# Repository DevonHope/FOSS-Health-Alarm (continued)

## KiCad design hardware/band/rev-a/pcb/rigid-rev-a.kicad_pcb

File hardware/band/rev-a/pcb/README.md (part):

# WakeBand rigid rev A (KiCad project)

4-layer 0.8 mm rigid board that replaces the flex design (archived in
`../../archive/flex-rev-a`). Routed, DRC clean, fab package in `fab/`. Last edited with
KiCad 10.0.3 (earlier revisions used 10.0.5; the file format is the same).

> **Before ordering rev A** (review 2026-11-08, `../../../reviews/2026-11-08`): the four layout items the
> review found were **fixed on 2026-11-08** by `scripts/review_fixes_2026_11_08.py`, and `fab/` was re-plotted
> (`scripts/mkfab.py`):
> - C203 pad 2 (GND, 116.12, 111.22) had one thermal spoke into GND_L1 (KiCad 10 `starved_thermal`): the
>   pad is boxed in by the PMIC_INT track, the SWDIO and VDD_2V0 vias and C203 pad 1, so it now has a solid
>   zone connection. Like R202.2, C401.2, R605.2 and C403.2 (review A-L2), that is a small tombstoning risk.
> - U202 (KTD2026): exposed pad 1.45 x 0.8 -> 1.2 x 0.65 mm, footprint renamed
>   `Kinetic_UTDFN-8_1.5x1.5mm_P0.4mm_EP1.2x0.65mm`. KiCad's DFN-8 pad is 0.7 x 1.2; 0.65 across the pin rows
>   keeps 0.2 mm to these 0.45 mm pins (0.7 would leave 0.175). Paste on the EP is two 0.45 x 0.48 mm
>   windows, 55 %. The pins, their tracks and the EP's GND link are unchanged.
> - The reference text of C208, U202 and D702, which was plotted 110-230 mm off the board in the top
>   silkscreen, is now on F.Fab next to each part, like the other references. No Gerber has anything outside
>   the outline.
> - The SWDCLK dock pad's via moved from the pad centre, where the spring pin lands, to the pad's left edge
>   (130.65, 101.1), on its F.Cu track, like the VIN and GND pads' edge vias.

| Item | Value |
| --- | --- |
| Board | 33 x 15 mm, 1 mm corner radius, 0.8 mm FR4, ENIG |
| Pod | printed case rev A in `../case` (one M2 screw); see below for the height stack |
| DRC | 0 violations, 0 unconnected, schematic parity 0 (1 documented exclusion); off-centre via ends checked as errors |
| Traces | straight or 45-degree segments only, 45-degree bends, every end on its pad or via centre (audit 2026-11-06, below) |
| ERC | 0 errors, 0 warnings |
| Vias | 140: 129 x 0.45/0.3 mm, 11 x 0.3/0.2 mm |
| Files | `rigid-rev-a-layout.pdf` (layers), `rigid-rev-a.pdf` (schematic), `fab/` |

## Stackup

JLCPCB JLC04081H-7628, 0.8 mm (also in `fab/gerbers/rigid-rev-a-job.gbrjob`):

| Layer | Use |
| --- | --- |
| F.Cu (L1, 35 um) | all SMT parts, two UART bench pads (J601 5-6, top edge), signal fan-out, GND pour |
| prepreg 7628, 0.21 mm | |
| In1.Cu (L2, 15 um) | solid GND, no tracks; no copper in the antenna keep-out |
| core 0.26 mm | |
| In2.Cu (L3, 15 um) | power jumps (VSYS, VBAT, VIN, VDD_2V0, LRA_P, nRESET) and signal routing; GND fill in the spare area |
| prepreg 7628, 0.21 mm | |
| B.Cu (L4, 35 um) | faces the cell and LRA: the four dock landing pads (J601 1-4), hand-solder pads TP201/TP202/TP501/TP502, JP201, signal routing, GND pour; no parts |

Track length by layer: F.Cu 208 mm, In2.Cu 205 mm, B.Cu 147 mm, In1.Cu 0.

## Orientation, outline and pod height

The board mounts **parts-side out** (changed 2026-11-06): F.Cu, with every
part, faces the case top, the pod's outer face. B.Cu has no parts and faces
the cell and the LRA, which sit between the board and the wrist.

**Dock contacts (changed 2026-11-07): four landing pads on B.** J601 pads
1-4 are Ø1.6 mm ENIG pads on B.Cu in a column at x 131.5, beside the LRA:
SWDCLK (y 101.1), SWDIO (103.3), GND (111.7), VIN (113.9). Four Mill-Max
0906-2 spring pins on the contact carrier in the wrist cover press on them
(see `../case` and `../contact-carrier`); nothing is soldered to
them. J601 pads 5-6 (UART_RX x 123.75, UART_TX x 121.75, y 101.6) stay on F
as bench test pads; the dock no longer carries UART (it uses SWD + RTT).
Coordinates below are KiCad board coordinates, with the board from
(100, 100) to (133, 115). The strip along the top edge (x 119.8-133) has
no parts, so the case top's land sits right on the board there and takes
the push of the top pair of spring pins.

Pod height, from the outer face (case rev A):

| Layer | mm |
| --- | --- |
| case top | 1.2 |
| tallest F part (L201, 0603 caps, SOD-123F) plus 0.2 mm | 1.3 |
| board | 0.8 |
| gap (B.Cu has no parts) | 0.2 |
| cell, up to | 5.0 |
| foam | 0.5 |
| wrist cover floor | 1.0 |
| **Total** | **about 10** (9 with a 4 mm cell) |

## Envelopes (Dwgs.User)

| Envelope | Where | Notes |
| --- | --- | --- |
| ISP2454 antenna keep-out | x 100-105, full height | rule area inside the U1 footprint: no tracks, vias or pours on any layer |
| 60 mAh cell, 17 x 13.5 mm | x 107-124, y 100.75-114.25 | under B; starts 2 mm past the keep-out; PCM and lead end at x = 124 |
| Ø8 LRA (Ø8.5 envelope) | centre (128.75, 107.5), x 124.5-133 | under B, far end of the board; circle top at y 103.25, bottom at 111.75 |

## 3D models

Every part on the board has a 3D model, except the test pads, the dock
pads, NT201 and JP201, which need none. KiCad 10 has no model for two
footprints, so `wakeband.3dshapes/` holds parametric ones (build123d; rebuild
with `pip install build123d`, then from this folder
`python wakeband.3dshapes/make_models.py wakeband.3dshapes`):

| Model | Used by | Size and source |
| --- | --- | --- |
| `InsightSiP_ISP2454_LGA-62_8x8mm.step` | U1 (also set in `wakeband.pretty`) | 8 x 8 x 1.0 mm, substrate plus overmould, pin-1 dot; size from the footprint |
| `Texas_DPY0002A_0.6x1mm_P0.65mm.step` | D602-D605 | 1.0 x 0.6 x 0.375 mm X1SON-2, bottom terminals, pin-1 band; TI MPSS034C |
| `LiPo_3.7V_60mAh_401215_PCM.step` | cell (off board) | 17 x 13 x 4.0 mm pouch with folded PCM at +X, lead stubs |
| `Vybronics_VG0832012_LRA_D8x3.25mm.step` | LRA (off board) | Ø8.0 x 3.25 mm can, lead tab at +X |
| `LED_TOGIALED_1615_RGB_CommonAnode.step` | D702 | 1.6 x 1.5 x 0.6 mm body and lens, pin-1 (anode) mark |
| `Kinetic_UTDFN-8_1.5x1.5mm_P0.4mm_EP1.45x0.8mm.step` | U202 (footprint now `..._EP1.2x0.65mm`; the package is the same) | 1.5 x 1.5 x 0.5 mm UTDFN-8, pin-1 dot, terminals |

The paths use `${KIPRJMOD}`. D602-D605 use the KiCad library footprint
`Package_SON:Texas_DPY0002A_0.6x1mm_P0.65mm`; "Update footprint from library"
puts back the library's model path, which has no file in KiCad 10.

`make_placed.py` places the cell and the LRA in the board's STEP frame,
under B.Cu with a 0.2 mm gap: the cell centred at (115.5, 107.5) with its
lead end at x = 124, and the LRA centred at (128.75, 107.5) with its lead tab
turned towards TP501. The leads run to TP201 (bottom right) and TP202 (top
right) and to TP501/TP502. A clash check against the board's STEP finds no
overlaps. The tallest F part is now 1.1 mm (SW201 was removed on
2026-11-07); the charge LED is 0.6 mm.

## Placement

- **U1 ISP2454** at the left end, antenna end in the keep-out strip.
- **U401 LIS2DW12** just right of the module's top corner. C401 and C402
  sit right of it, 1.0 mm of track from pins 9 and 10; their GND pads share
  one via, and U401's GND pads 5-8 share another.
- **U201 nPM1304** in the middle. The BUCK1 parts sit left of it (see
  "Buck loop" below).
- **Charger caps** stacked right of U201, each beside its pin: C206
  (VBUSOUT, pin 22), C201 (VIN, pin 21), C205 (VSYS, pin 20), C202 (VBAT,
  pin 19). Their GND pads are joined by an F.Cu spine with three vias to
  In1 between the pads. R202 (VSET1) and R201 (DNP) sit below the stack.
  C203 sits under PMIC pin 12, offset left so pins 13-15 can escape.
- **JP201** (I_BAT jumper) on B in the bottom-right corner, between the
  cell's lead end and TP201, outside the cell and LRA outlines, so it can
  be cut for current measurement with the cell fitted.
- **Dock landing pads** J601 on B at x 131.5 (see Orientation). Their
  protection parts stay along the bottom edge: R601-R604 and D602-D605 (TI
  DPY package) between the module and D601 (VIN TVS).
- **U501 DRV2605L** at the right end over the LRA envelope, with C501, C502.
- **Hand-solder pads** on B (the cell side), 0.5 mm to other copper and
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
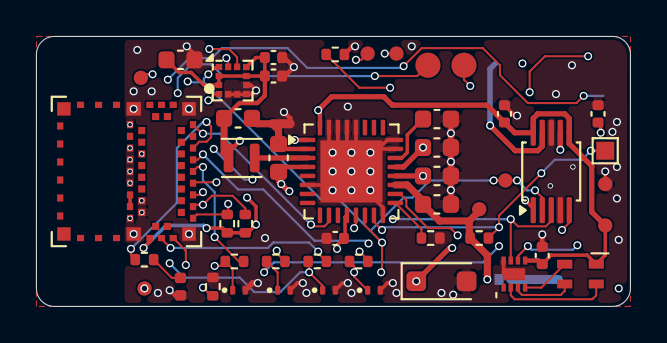
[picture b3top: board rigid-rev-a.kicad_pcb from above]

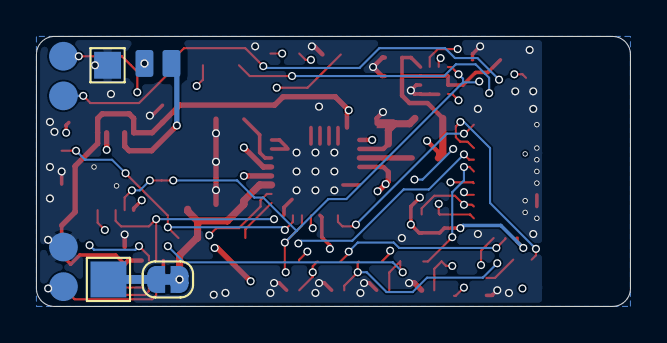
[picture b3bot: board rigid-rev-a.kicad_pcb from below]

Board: 4 copper layers, 33.0 x 15.0 mm, 53 parts (5 on the bottom side), 36 nets.

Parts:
C201, C206: 1uF 50V X5R; C_0603_1608Metric
C202: 2.2uF 16V X5R; C_0603_1608Metric
C203, C401, C402: 100nF; C_0402_1005Metric
C204, C205, C207, C403: 10uF 25V X5R; C_0603_1608Metric
C208, C501, C502: 1uF 25V X5R; C_0402_1005Metric
D601: SMF12A (TVS); D_SOD-123F
D602, D603, D604, D605: TPD1E10B06; Texas_DPY0002A_0.6x1mm_P0.65mm
D701: red DNP; LED_0402_1005Metric
D702: TJ-S1615SW6TGLCCYRGB-A5; LED_TOGIALED_1615_RGB_CommonAnode
J601: Dock landing pads; DockLanding_4xB_D1.6mm_2xUART
JP201: I_BAT; SolderJumper-2_P1.3mm_Bridged_RoundedPad1.0x1.5mm
L201: 2.2uH; L_Murata_DFE201610P
NT201: NetTie; NetTie-2_SMD_Pad0.5mm
R201: 100k DNP; R_0402_1005Metric
R202: 68k 1%; R_0402_1005Metric
R203, R204: 4.7k; R_0402_1005Metric
R601, R602, R603, R604: 100; R_0402_1005Metric
R605: 100k; R_0402_1005Metric
R701: 1k DNP; R_0402_1005Metric
TH201: 10k B3380; R_0402_1005Metric
TP201: BAT+ pad; TestPoint_Pad_2.0x2.0mm
TP202: BAT- pad; TestPoint_Pad_1.5x1.5mm
TP203: SHPHLD; TestPoint_Pad_1.0x1.0mm
TP401: ACC_INT2; TestPoint_Pad_D0.8mm
TP501: LRA+; Pad_SMD_1.0x1.5mm
TP502: LRA-; Pad_SMD_1.0x1.5mm
TP701: nRESET; TestPoint_Pad_D0.8mm
TP702: I2C_SDA; TestPoint_Pad_D0.8mm
TP703: I2C_SCL; TestPoint_Pad_D0.8mm
TP704: VDD_2V0; TestPoint_Pad_D0.8mm
TP705: VSYS; TestPoint_Pad_D0.8mm
TP706: VBAT; TestPoint_Pad_D0.8mm
TP707: GND; TestPoint_Pad_D0.8mm
U1: ISP2454-LX; InsightSiP_ISP2454_LGA-62_8x8mm
U201: nPM1304-QEAA; QFN-32-1EP_5x5mm_P0.5mm_EP3.45x3.45mm
U202: KTD2026EWE-TR; Kinetic_UTDFN-8_1.5x1.5mm_P0.4mm_EP1.2x0.65mm
U401: LIS2DW12TR; LGA-12_2x2mm_P0.5mm
U501: DRV2605LDGSR; TSSOP-10_3x3mm_P0.5mm

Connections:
/debug/LED_A: D701.2, R701.2
/dock/PAD_RX: D604.1, J601.5, R603.1
/dock/PAD_SWDCLK: D602.1, J601.3, R601.1
/dock/PAD_SWDIO: D603.1, J601.4, R602.1
/dock/PAD_TX: D605.1, J601.6, R604.1
/haptics/LRA_N: TP502.1, U501.9
/haptics/LRA_P: TP501.1, U501.7
/haptics/REG: C502.1, U501.1
/power/BATT_P: JP201.1, TP201.1
/power/LED_B: D702.2, U202.4
/power/LED_G: D702.3, U202.3
/power/LED_R: D702.4, U202.2
/power/NTC: TH201.1, U201.18
/power/PVSS1: C204.2, C207.2, NT201.1, U201.2
/power/SHPHLD: R201.2, TP203.1, U201.15
/power/SW1: L201.1, U201.3
/power/VBUSOUT: C206.1, U201.22
/power/VSET1: R202.1, U201.17
ACC_INT1: U1.36, U401.12
ACC_INT2: TP401.1, U401.11
ANT_LINK: U1.20, U1.22
GND: C201.2, C202.2, C203.2, C205.2, C206.2, C208.2, C401.2, C402.2, C403.2, C501.2, C502.2, D601.2, D602.2, D603.2, D604.2, D605.2, D701.1, J601.2, NT201.2, R202.2, R605.2, TH201.2, TP202.1, TP707.1, U1.1, U1.7, U1.8, U1.12, U1.14, U1.16, U1.18, U1.21, U1.23, U1.24, U1.25, U1.31, U201.6, U201.16, U201.23, U201.24, U201.28, U201.29, U201.30, U201.31, U201.33, U202.8, U202.9, U401.5, U401.6, U401.7, U401.8, U501.4, U501.8
HAPT_EN: U1.42, U501.5
I2C_SCL: R204.2, TP703.1, U1.34, U201.14, U202.6, U401.1, U501.2
I2C_SDA: R203.2, TP702.1, U1.32, U201.13, U202.7, U401.4, U501.3
LED_DBG: R701.1, U1.44
PMIC_INT: U1.48, U201.10
SWDCLK: R601.2, U1.30
SWDIO: R602.2, U1.28
UART_RX: R603.2, R605.1, U1.38
UART_TX: R604.2, U1.40
VBAT: C202.1, JP201.2, R201.1, TP706.1, U201.19
VDD_2V0: C203.1, C207.1, C401.1, C402.1, C403.1, L201.2, R203.1, R204.1, TP704.1, U1.26, U201.1, U201.12, U401.2, U401.3, U401.9, U401.10
VIN: C201.1, D601.1, J601.1, U201.21
VSYS: C204.1, C205.1, C208.1, C501.1, D702.1, TP705.1, U201.4, U201.20, U201.32, U202.5, U501.6, U501.10
nRESET: TP701.1, U1.13

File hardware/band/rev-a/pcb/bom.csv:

"Comment","Designator","Footprint","LCSC","MPN","Qty","DNP"
"1uF 50V X5R","C201,C206","Capacitor_SMD:C_0603_1608Metric","C15849","","2",""
"2.2uF 16V X5R","C202","Capacitor_SMD:C_0603_1608Metric","C23630","","1",""
"100nF","C203,C401,C402","Capacitor_SMD:C_0402_1005Metric","C1525","","3",""
"10uF 25V X5R","C204,C205,C207,C403","Capacitor_SMD:C_0603_1608Metric","C96446","","4",""
"1uF 25V X5R","C208,C501,C502","Capacitor_SMD:C_0402_1005Metric","C52923","","3",""
"SMF12A (TVS)","D601","Diode_SMD:D_SOD-123F","C207255","Littelfuse SMF12A","1",""
"TPD1E10B06","D602,D603,D604,D605","Package_SON:Texas_DPY0002A_0.6x1mm_P0.65mm","C48260","TI TPD1E10B06DPYR","4",""
"TJ-S1615SW6TGLCCYRGB-A5 (RGB LED, common anode)","D702","wakeband:LED_TOGIALED_1615_RGB_CommonAnode","C273610","TOGIALED TJ-S1615SW6TGLCCYRGB-A5","1",""
"red DNP","D701","LED_SMD:LED_0402_1005Metric","C25503345","XINGLIGHT XL-1005SURC","1","DNP"
"2.2uH","L201","Inductor_SMD:L_Murata_DFE201610P","C337891","Murata DFE201610E-2R2M","1",""
"100k DNP","R201","Resistor_SMD:R_0402_1005Metric","C25741","","1","DNP"
"68k 1%","R202","Resistor_SMD:R_0402_1005Metric","C36871","","1",""
"4.7k","R203,R204","Resistor_SMD:R_0402_1005Metric","C25900","","2",""
"100","R601,R602,R603,R604","Resistor_SMD:R_0402_1005Metric","C25076","","4",""
"100k","R605","Resistor_SMD:R_0402_1005Metric","C25741","","1",""
"1k DNP","R701","Resistor_SMD:R_0402_1005Metric","C11702","","1","DNP"
"10k B3380","TH201","Resistor_SMD:R_0402_1005Metric","C77131","Murata NCP15XH103F03RC","1",""
"ISP2454-LX","U1","wakeband:InsightSiP_ISP2454_LGA-62_8x8mm","","","1",""
"nPM1304-QEAA","U201","Package_DFN_QFN:QFN-32-1EP_5x5mm_P0.5mm_EP3.45x3.45mm","","","1",""
"KTD2026EWE-TR (I2C RGB LED driver; Digi-Key, no LCSC listing)","U202","wakeband:Kinetic_UTDFN-8_1.5x1.5mm_P0.4mm_EP1.45x0.8mm","","Kinetic KTD2026EWE-TR","1",""
"LIS2DW12TR","U401","Package_LGA:LGA-12_2x2mm_P0.5mm","C189624","","1",""
"DRV2605LDGSR","U501","Package_SO:TSSOP-10_3x3mm_P0.5mm","C527464","","1",""
"60mAh 3.7V protected LiPo, ~16x13x4-5 mm, wire leads (hand-soldered to TP201/TP202, not assembled; alt. Ampul 401215)","BT1 (off-board)","","","X2 Robotics 3.7V 60mAh LiPo","1","not assembled"

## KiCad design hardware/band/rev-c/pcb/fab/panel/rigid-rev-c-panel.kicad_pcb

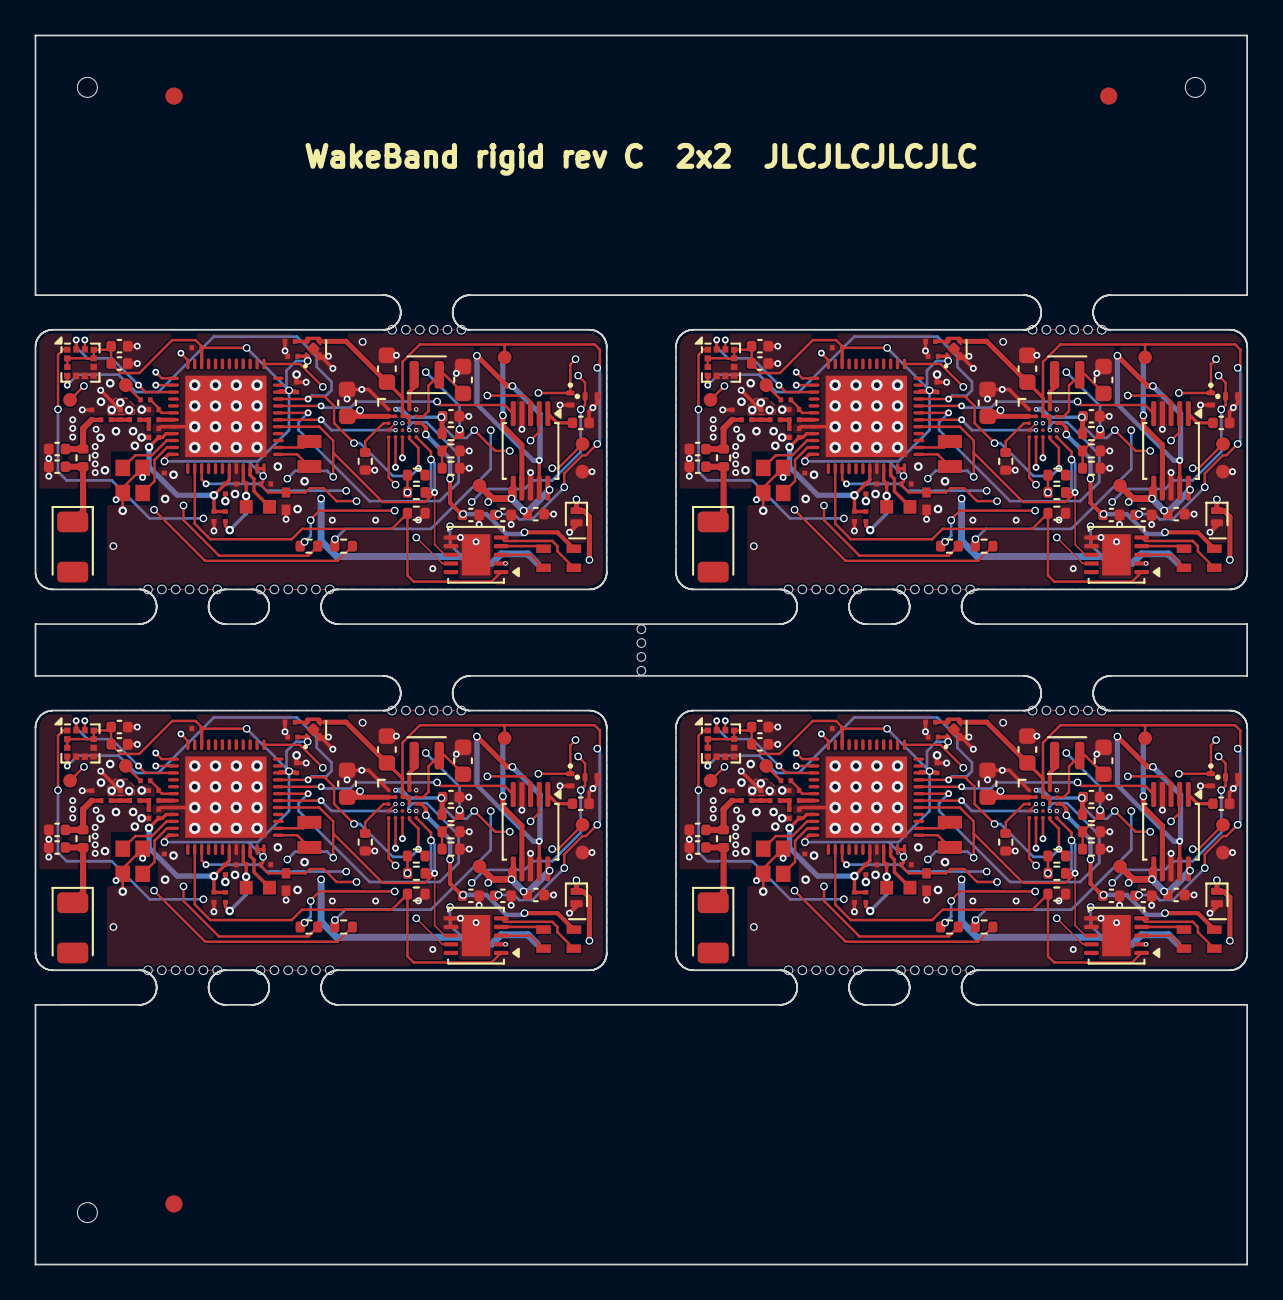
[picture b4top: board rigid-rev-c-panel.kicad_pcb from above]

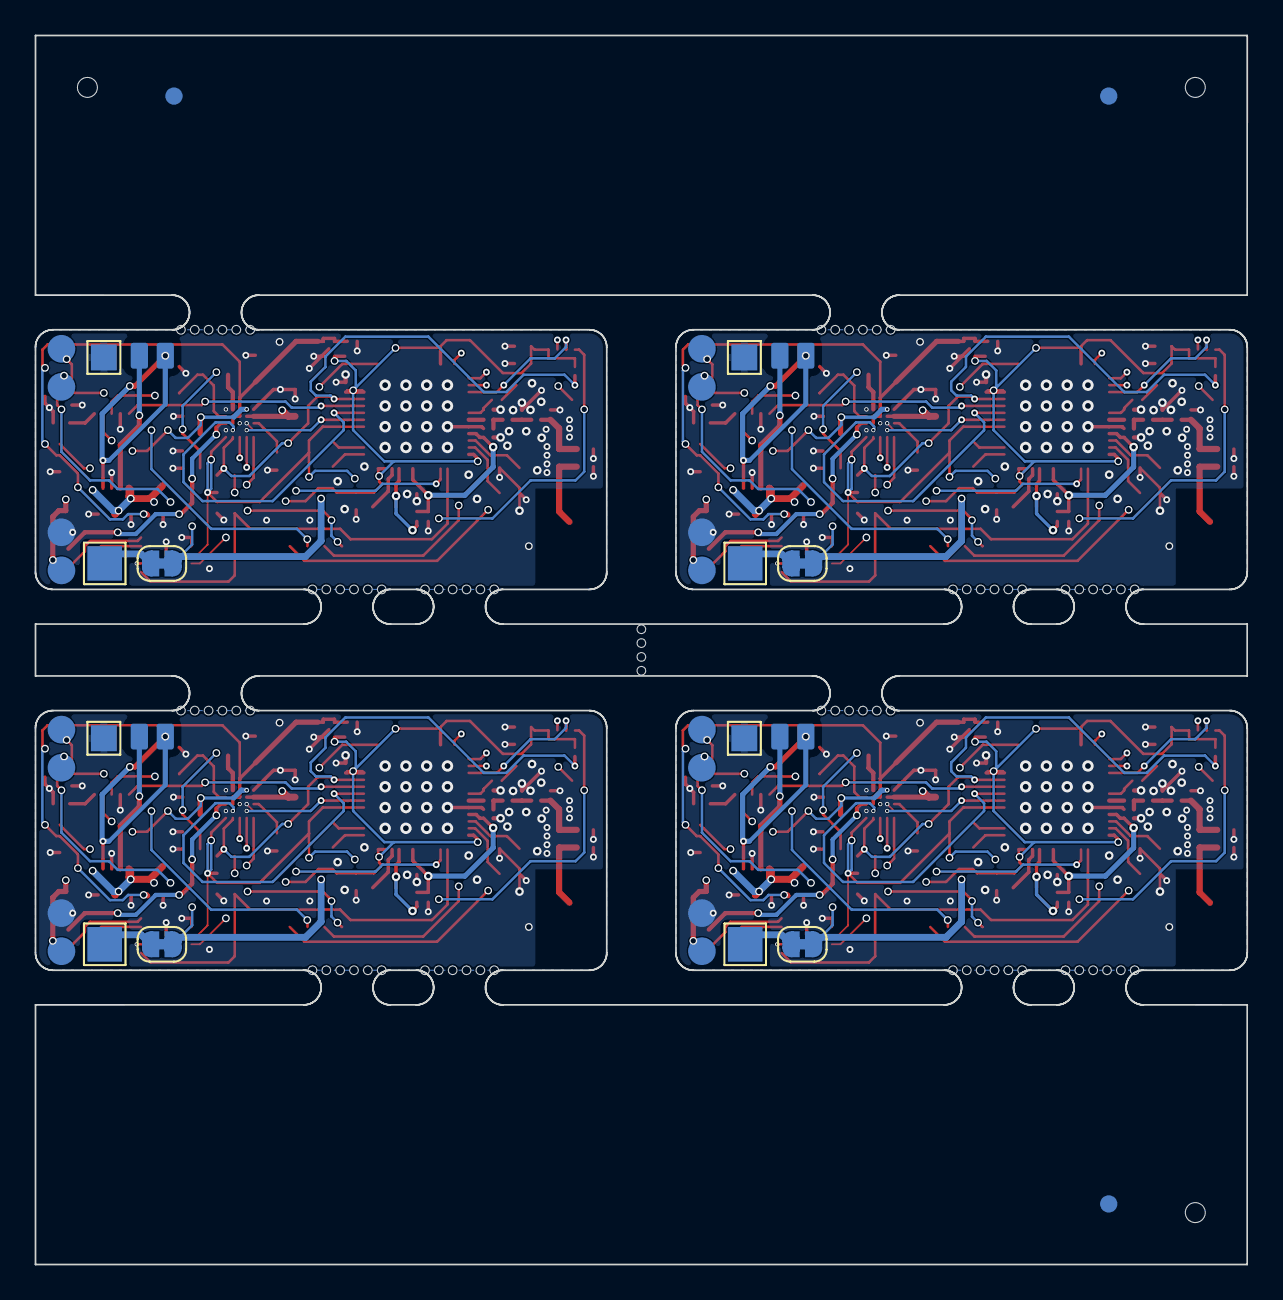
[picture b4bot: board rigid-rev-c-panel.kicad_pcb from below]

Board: 4 copper layers, 70.0 x 71.0 mm, 361 parts (23 on the bottom side), 184 nets.

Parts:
AE1_0, AE1_1, AE1_2, AE1_3: 2450AT18A0100001E; Johanson_2450AT18x100
C1_0, C1_1, C1_2, C1_3, C2_0, C2_1, C2_2, C2_3: 2.2uF; Nordic_CAPC0603X03L_C
C3_0, C3_1, C3_2, C3_3: 10uF; Nordic_CAPC1005X04L
C4_0, C4_1, C4_2, C4_3, C7_0, C7_1, C7_2, C7_3, C8_0, C8_1, C8_2, C8_3, C10_0, C10_1, C10_2, C10_3: 100nF; Nordic_CAPC0603X03L_C
C5_0, C5_1, C5_2, C5_3: 2.2nF; Nordic_CAPC0603X03L_C
C6_0, C6_1, C6_2, C6_3: 1.5pF; Nordic_CAPC0603X03L_C
C9_0, C9_1, C9_2, C9_3: 2.0pF; Nordic_CAPC0603X03L_C
C11_0, C11_1, C11_2, C11_3: 0.3pF; Nordic_CAPC0603X03L_C
C12_0, C12_1, C12_2, C12_3: 10nF; Nordic_CAPC0603X03L_C
C13_0, C13_1, C13_2, C13_3: 3.9pF; Nordic_CAPC0603X03L_C
C14_0, C14_1, C14_2, C14_3, C15_0, C15_1, C15_2, C15_3: DNP; C_0402_1005Metric
C201_0, C201_1, C201_2, C201_3, C208_0, C208_1, C208_2, C208_3, C501_0, C501_1, C501_2, C501_3, C502_0, C502_1, C502_2, C502_3: 1uF; C_0402_1005Metric
C202_0, C202_1, C202_2, C202_3: 2.2uF; C_0603_1608Metric
C205_0, C205_1, C205_2, C205_3, C206_0, C206_1, C206_2, C206_3: 10uF; C_0603_1608Metric
C209_0, C209_1, C209_2, C209_3, C401_0, C401_1, C401_2, C401_3, C402_0, C402_1, C402_2, C402_3: 100nF; C_0402_1005Metric
C210_0, C210_1, C210_2, C210_3, C211_0, C211_1, C211_2, C211_3: 1uF; Nordic_CAPC0603X03L_C
D601_0, D601_1, D601_2, D601_3: ESD5681N07; D_SOD-882
D602_0, D602_1, D602_2, D602_3, D603_0, D603_1, D603_2, D603_3: TPD1E10B06; Texas_DPY0002A_0.6x1mm_P0.65mm
D702_0, D702_1, D702_2, D702_3: TJ-S1615SW6TGLCCYRGB-A5; LED_TOGIALED_1615_RGB_CommonAnode
FB1_0, FB1_1, FB1_2, FB1_3: 120R@100MHz; Nordic_INDC0603X03L_C
J601_0, J601_1, J601_2, J601_3: Dock landing pads; DockLanding_4xB_D1.6mm
JP201_0, JP201_1, JP201_2, JP201_3: I_BAT; SolderJumper-2_P1.3mm_Bridged_RoundedPad1.0x1.5mm
KiKit_FID_B_1, KiKit_FID_B_2, KiKit_FID_B_3: Fiducial
KiKit_FID_T_1, KiKit_FID_T_2, KiKit_FID_T_3: Fiducial
KiKit_MB_1_1, KiKit_MB_1_2, KiKit_MB_1_3, KiKit_MB_1_4, KiKit_MB_1_5, KiKit_MB_1_6, KiKit_MB_2_1, KiKit_MB_2_2, KiKit_MB_2_3, KiKit_MB_2_4, KiKit_MB_2_5, KiKit_MB_2_6, KiKit_MB_3_1, KiKit_MB_3_2, KiKit_MB_3_3, KiKit_MB_3_4, KiKit_MB_3_5, KiKit_MB_3_6, KiKit_MB_4_1, KiKit_MB_4_2, KiKit_MB_4_3, KiKit_MB_4_4, KiKit_MB_4_5, KiKit_MB_4_6, KiKit_MB_5_1, KiKit_MB_5_2, KiKit_MB_5_3, KiKit_MB_5_4, KiKit_MB_5_5, KiKit_MB_5_6, KiKit_MB_6_1, KiKit_MB_6_2, KiKit_MB_6_3, KiKit_MB_6_4, KiKit_MB_6_5, KiKit_MB_6_6, KiKit_MB_7_1, KiKit_MB_7_2, KiKit_MB_7_3, KiKit_MB_7_4, KiKit_MB_7_5, KiKit_MB_7_6, KiKit_MB_8_1, KiKit_MB_8_2, KiKit_MB_8_3, KiKit_MB_8_4, KiKit_MB_8_5, KiKit_MB_8_6, KiKit_MB_9_1, KiKit_MB_9_2, KiKit_MB_9_3, KiKit_MB_9_4, KiKit_MB_9_5, KiKit_MB_9_6, KiKit_MB_10_1, KiKit_MB_10_2, KiKit_MB_10_3, KiKit_MB_10_4, KiKit_MB_10_5, KiKit_MB_10_6, KiKit_MB_11_1, KiKit_MB_11_2, KiKit_MB_11_3, KiKit_MB_11_4, KiKit_MB_11_5, KiKit_MB_11_6, KiKit_MB_12_1, KiKit_MB_12_2, KiKit_MB_12_3, KiKit_MB_12_4, KiKit_MB_12_5, KiKit_MB_12_6, KiKit_MB_13_2, KiKit_MB_13_3, KiKit_MB_13_4, KiKit_MB_13_5: NPTH
KiKit_TO_1, KiKit_TO_2, KiKit_TO_3: NPTH
L1_0, L1_1, L1_2, L1_3: 4.7uH; Nordic_INDC1608X06L
L2_0, L2_1, L2_2, L2_3: 2.7nH; Nordic_INDC0603X03L_C
L3_0, L3_1, L3_2, L3_3, L4_0, L4_1, L4_2, L4_3: 3.5nH; Nordic_INDC0603X03L_C
L201_0, L201_1, L201_2, L201_3: 2.2uH; L_Murata_DFE201610P
R1_0, R1_1, R1_2, R1_3: 1k; Nordic_RESC0603X03L_C
R2_0, R2_1, R2_2, R2_3: 0R; R_0402_1005Metric
R202_0, R202_1, R202_2, R202_3: 6.65k; R_0402_1005Metric
R203_0, R203_1, R203_2, R203_3, R204_0, R204_1, R204_2, R204_3: 4.7k; R_0402_1005Metric
R207_0, R207_1, R207_2, R207_3: 14k; R_0402_1005Metric
R208_0, R208_1, R208_2, R208_3: 14.3k; R_0402_1005Metric
R211_0, R211_1, R211_2, R211_3: 100k; R_0402_1005Metric
R601_0, R601_1, R601_2, R601_3, R602_0, R602_1, R602_2, R602_3: 100; R_0402_1005Metric
TH201_0, TH201_1, TH201_2, TH201_3: 10k B3380; R_0402_1005Metric
TP201_0, TP201_1, TP201_2, TP201_3: BAT+ pad; TestPoint_Pad_2.0x2.0mm
TP202_0, TP202_1, TP202_2, TP202_3: BAT- pad; TestPoint_Pad_1.5x1.5mm
TP203_0, TP203_1, TP203_2, TP203_3: MR; TestPoint_Pad_D0.8mm
TP401_0, TP401_1, TP401_2, TP401_3: ACC_INT2; TestPoint_Pad_D0.8mm
TP501_0, TP501_1, TP501_2, TP501_3: LRA+; Pad_SMD_1.0x1.5mm
TP502_0, TP502_1, TP502_2, TP502_3: LRA-; Pad_SMD_1.0x1.5mm
TP701_0, TP701_1, TP701_2, TP701_3: nRESET; TestPoint_Pad_D0.8mm
TP705_0, TP705_1, TP705_2, TP705_3: PMID; TestPoint_Pad_D0.8mm
TP706_0, TP706_1, TP706_2, TP706_3: VBAT; TestPoint_Pad_D0.8mm
TP707_0, TP707_1, TP707_2, TP707_3: GND; TestPoint_Pad_D0.8mm
U1_0, U1_1, U1_2, U1_3: nRF54L10-QFAA; Nordic_QFN40P600X600X90-48N
U201_0, U201_1, U201_2, U201_3: BQ25125; TI_DSBGA-25_2.5x2.5mm_Layout5x5_P0.4mm
U202_0, U202_1, U202_2, U202_3: IS31FL3193; DFN-10-1EP_3x3mm_P0.5mm_EP1.65x2.38mm
U203_0, U203_1, U203_2, U203_3: TPS7A0220; Texas_X2SON-4_1x1mm_P0.65mm_SilkTrim
U401_0, U401_1, U401_2, U401_3: LIS2DW12TR; LGA-12_2x2mm_P0.5mm
U501_0, U501_1, U501_2, U501_3: DRV2605LDGSR; TSSOP-10_3x3mm_P0.5mm
X1_0, X1_1, X1_2, X1_3: 32.768kHz 9pF; Nordic_XTAL_2012
X2_0, X2_1, X2_2, X2_3: 32MHz 8pF; Nordic_BT-XTAL_2016

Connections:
Board_0-/ACC_INT1: U1_0.27, U401_0.12
Board_0-/ACC_INT2: TP401_0.1, U1_0.24, U401_0.11
Board_0-/ANT: L2_0.1, U1_0.31
Board_0-/ANT_FEED: AE1_0.1, C15_0.1, R2_0.2
Board_0-/BATT_P: JP201_0.1, TP201_0.1
Board_0-/CHG_CD: U1_0.39, U201_0.E2
Board_0-/CHG_MR: TP203_0.1, U201_0.E1
Board_0-/DCC: L1_0.1, U1_0.46
Board_0-/DECA: C2_0.2, C5_0.2, C12_0.2, FB1_0.2, U1_0.33, U1_0.43
Board_0-/DECD: C1_0.2, FB1_0.1, L1_0.2, U1_0.45
Board_0-/DOCK_PG: U1_0.7, U201_0.D4
Board_0-/GND: C1_0.1, C2_0.1, C3_0.1, C4_0.2, C5_0.1, C6_0.1, C7_0.2, C8_0.2, C9_0.1, C10_0.2, C11_0.1, C12_0.1, C13_0.1, C14_0.2, C15_0.2, C201_0.2, C202_0.2, C205_0.2, C206_0.2, C208_0.2, C209_0.2, C210_0.2, C211_0.2, C401_0.2, C402_0.2, C501_0.2, C502_0.2, D601_0.2, D602_0.2, D603_0.2, J601_0.2, R202_0.2, R208_0.2, R211_0.2, TH201_0.2, TP202_0.1, TP707_0.1, U1_0.32, U1_0.44, U1_0.49, U201_0.A1, U201_0.A5, U201_0.C2, U201_0.D1, U201_0.D5, U202_0.6, U202_0.7, U202_0.11, U203_0.2, U203_0.5, U401_0.5, U401_0.6, U401_0.7, U401_0.8, U501_0.4, U501_0.8, X2_0.2, X2_0.4
Board_0-/HAPT_EN: U1_0.8, U501_0.5
Board_0-/I2C_SCL: R204_0.2, U1_0.5, U201_0.E5, U202_0.8, U401_0.1, U501_0.2
Board_0-/I2C_SDA: R203_0.2, U1_0.9, U201_0.E4, U202_0.9, U401_0.4, U501_0.3
Board_0-/ISET: R202_0.1, U201_0.C1
Board_0-/LED_B: D702_0.2, U202_0.4
Board_0-/LED_EN: R211_0.1, U1_0.38, U202_0.1
Board_0-/LED_G: D702_0.3, U202_0.3
Board_0-/LED_R: D702_0.4, U202_0.5
Board_0-/LRA_N: TP502_0.1, U501_0.9
Board_0-/LRA_P: TP501_0.1, U501_0.7
Board_0-/LS_CTRL: U1_0.13, U201_0.E3
Board_0-/PAD_SWDCLK: D602_0.1, J601_0.3, R601_0.1
Board_0-/PAD_SWDIO: D603_0.1, J601_0.4, R602_0.1
Board_0-/PMIC_INT: U1_0.6, U201_0.D2
Board_0-/PMID: C206_0.1, C209_0.1, C210_0.1, TP705_0.1, U201_0.A3, U201_0.B3, U201_0.B4, U201_0.C4, U202_0.2, U203_0.3, U203_0.4
Board_0-/REG: C502_0.1, U501_0.1
Board_0-/RF1: C6_0.2, L2_0.2, L3_0.1
Board_0-/RF2: C9_0.2, L3_0.2, L4_0.1
Board_0-/RF_50: C11_0.2, C14_0.1, L4_0.2, R2_0.1
Board_0-/SW: L201_0.1, U201_0.A4
Board_0-/SWDCLK: R601_0.2, U1_0.26
Board_0-/SWDIO: R602_0.2, U1_0.25
Board_0-/TS: R207_0.2, R208_0.1, TH201_0.1, U201_0.C3
Board_0-/VBAT: C202_0.1, C501_0.1, JP201_0.2, TP706_0.1, U201_0.B1, U201_0.B2, U501_0.6, U501_0.10
Board_0-/VDD_2V0: C3_0.2, C4_0.1, C7_0.1, C8_0.1, C10_0.1, C211_0.1, C401_0.1, C402_0.1, R203_0.1, R204_0.1, U1_0.10, U1_0.22, U1_0.36, U1_0.47, U1_0.48, U203_0.1, U401_0.2, U401_0.3, U401_0.9, U401_0.10
Board_0-/VIN: C201_0.1, D601_0.1, J601_0.1, R207_0.1, U201_0.A2
Board_0-/VLED: C208_0.1, D702_0.1, U201_0.C5
Board_0-/VSYS: C205_0.1, L201_0.2, U201_0.B5
Board_0-/XC1: U1_0.34, X2_0.1
Board_0-/XC2: U1_0.35, X2_0.3
Board_0-/XL1: U1_0.1, X1_0.2
Board_0-/XL2: U1_0.2, X1_0.1
Board_0-/nRESET: R1_0.2, TP701_0.1
Board_0-/nRESET_IC: C13_0.2, R1_0.1, U1_0.30
Board_1-/ACC_INT1: U1_1.27, U401_1.12
Board_1-/ACC_INT2: TP401_1.1, U1_1.24, U401_1.11
Board_1-/ANT: L2_1.1, U1_1.31
Board_1-/ANT_FEED: AE1_1.1, C15_1.1, R2_1.2
Board_1-/BATT_P: JP201_1.1, TP201_1.1
Board_1-/CHG_CD: U1_1.39, U201_1.E2
Board_1-/CHG_MR: TP203_1.1, U201_1.E1
Board_1-/DCC: L1_1.1, U1_1.46
Board_1-/DECA: C2_1.2, C5_1.2, C12_1.2, FB1_1.2, U1_1.33, U1_1.43
Board_1-/DECD: C1_1.2, FB1_1.1, L1_1.2, U1_1.45
Board_1-/DOCK_PG: U1_1.7, U201_1.D4
Board_1-/GND: C1_1.1, C2_1.1, C3_1.1, C4_1.2, C5_1.1, C6_1.1, C7_1.2, C8_1.2, C9_1.1, C10_1.2, C11_1.1, C12_1.1, C13_1.1, C14_1.2, C15_1.2, C201_1.2, C202_1.2, C205_1.2, C206_1.2, C208_1.2, C209_1.2, C210_1.2, C211_1.2, C401_1.2, C402_1.2, C501_1.2, C502_1.2, D601_1.2, D602_1.2, D603_1.2, J601_1.2, R202_1.2, R208_1.2, R211_1.2, TH201_1.2, TP202_1.1, TP707_1.1, U1_1.32, U1_1.44, U1_1.49, U201_1.A1, U201_1.A5, U201_1.C2, U201_1.D1, U201_1.D5, U202_1.6, U202_1.7, U202_1.11, U203_1.2, U203_1.5, U401_1.5, U401_1.6, U401_1.7, U401_1.8, U501_1.4, U501_1.8, X2_1.2, X2_1.4
Board_1-/HAPT_EN: U1_1.8, U501_1.5
Board_1-/I2C_SCL: R204_1.2, U1_1.5, U201_1.E5, U202_1.8, U401_1.1, U501_1.2
Board_1-/I2C_SDA: R203_1.2, U1_1.9, U201_1.E4, U202_1.9, U401_1.4, U501_1.3
Board_1-/ISET: R202_1.1, U201_1.C1
Board_1-/LED_B: D702_1.2, U202_1.4
Board_1-/LED_EN: R211_1.1, U1_1.38, U202_1.1
Board_1-/LED_G: D702_1.3, U202_1.3
Board_1-/LED_R: D702_1.4, U202_1.5
Board_1-/LRA_N: TP502_1.1, U501_1.9
Board_1-/LRA_P: TP501_1.1, U501_1.7
Board_1-/LS_CTRL: U1_1.13, U201_1.E3
Board_1-/PAD_SWDCLK: D602_1.1, J601_1.3, R601_1.1
Board_1-/PAD_SWDIO: D603_1.1, J601_1.4, R602_1.1
Board_1-/PMIC_INT: U1_1.6, U201_1.D2
Board_1-/PMID: C206_1.1, C209_1.1, C210_1.1, TP705_1.1, U201_1.A3, U201_1.B3, U201_1.B4, U201_1.C4, U202_1.2, U203_1.3, U203_1.4
Board_1-/REG: C502_1.1, U501_1.1
Board_1-/RF1: C6_1.2, L2_1.2, L3_1.1
Board_1-/RF2: C9_1.2, L3_1.2, L4_1.1
Board_1-/RF_50: C11_1.2, C14_1.1, L4_1.2, R2_1.1
Board_1-/SW: L201_1.1, U201_1.A4
Board_1-/SWDCLK: R601_1.2, U1_1.26
Board_1-/SWDIO: R602_1.2, U1_1.25
Board_1-/TS: R207_1.2, R208_1.1, TH201_1.1, U201_1.C3
Board_1-/VBAT: C202_1.1, C501_1.1, JP201_1.2, TP706_1.1, U201_1.B1, U201_1.B2, U501_1.6, U501_1.10
Board_1-/VDD_2V0: C3_1.2, C4_1.1, C7_1.1, C8_1.1, C10_1.1, C211_1.1, C401_1.1, C402_1.1, R203_1.1, R204_1.1, U1_1.10, U1_1.22, U1_1.36, U1_1.47, U1_1.48, U203_1.1, U401_1.2, U401_1.3, U401_1.9, U401_1.10
Board_1-/VIN: C201_1.1, D601_1.1, J601_1.1, R207_1.1, U201_1.A2
Board_1-/VLED: C208_1.1, D702_1.1, U201_1.C5
Board_1-/VSYS: C205_1.1, L201_1.2, U201_1.B5
Board_1-/XC1: U1_1.34, X2_1.1
Board_1-/XC2: U1_1.35, X2_1.3
Board_1-/XL1: U1_1.1, X1_1.2
Board_1-/XL2: U1_1.2, X1_1.1
Board_1-/nRESET: R1_1.2, TP701_1.1
Board_1-/nRESET_IC: C13_1.2, R1_1.1, U1_1.30
Board_2-/ACC_INT1: U1_2.27, U401_2.12
Board_2-/ACC_INT2: TP401_2.1, U1_2.24, U401_2.11
Board_2-/ANT: L2_2.1, U1_2.31
Board_2-/ANT_FEED: AE1_2.1, C15_2.1, R2_2.2
Board_2-/BATT_P: JP201_2.1, TP201_2.1
Board_2-/CHG_CD: U1_2.39, U201_2.E2
Board_2-/CHG_MR: TP203_2.1, U201_2.E1
Board_2-/DCC: L1_2.1, U1_2.46
Board_2-/DECA: C2_2.2, C5_2.2, C12_2.2, FB1_2.2, U1_2.33, U1_2.43
Board_2-/DECD: C1_2.2, FB1_2.1, L1_2.2, U1_2.45
Board_2-/DOCK_PG: U1_2.7, U201_2.D4
Board_2-/GND: C1_2.1, C2_2.1, C3_2.1, C4_2.2, C5_2.1, C6_2.1, C7_2.2, C8_2.2, C9_2.1, C10_2.2, C11_2.1, C12_2.1, C13_2.1, C14_2.2, C15_2.2, C201_2.2, C202_2.2, C205_2.2, C206_2.2, C208_2.2, C209_2.2, C210_2.2, C211_2.2, C401_2.2, C402_2.2, C501_2.2, C502_2.2, D601_2.2, D602_2.2, D603_2.2, J601_2.2, R202_2.2, R208_2.2, R211_2.2, TH201_2.2, TP202_2.1, TP707_2.1, U1_2.32, U1_2.44, U1_2.49, U201_2.A1, U201_2.A5, U201_2.C2, U201_2.D1, U201_2.D5, U202_2.6, U202_2.7, U202_2.11, U203_2.2, U203_2.5, U401_2.5, U401_2.6, U401_2.7, U401_2.8, U501_2.4, U501_2.8, X2_2.2, X2_2.4
Board_2-/HAPT_EN: U1_2.8, U501_2.5
Board_2-/I2C_SCL: R204_2.2, U1_2.5, U201_2.E5, U202_2.8, U401_2.1, U501_2.2
Board_2-/I2C_SDA: R203_2.2, U1_2.9, U201_2.E4, U202_2.9, U401_2.4, U501_2.3
Board_2-/ISET: R202_2.1, U201_2.C1
Board_2-/LED_B: D702_2.2, U202_2.4
Board_2-/LED_EN: R211_2.1, U1_2.38, U202_2.1
Board_2-/LED_G: D702_2.3, U202_2.3
Board_2-/LED_R: D702_2.4, U202_2.5
Board_2-/LRA_N: TP502_2.1, U501_2.9
Board_2-/LRA_P: TP501_2.1, U501_2.7
Board_2-/LS_CTRL: U1_2.13, U201_2.E3
Board_2-/PAD_SWDCLK: D602_2.1, J601_2.3, R601_2.1
Board_2-/PAD_SWDIO: D603_2.1, J601_2.4, R602_2.1
Board_2-/PMIC_INT: U1_2.6, U201_2.D2
Board_2-/PMID: C206_2.1, C209_2.1, C210_2.1, TP705_2.1, U201_2.A3, U201_2.B3, U201_2.B4, U201_2.C4, U202_2.2, U203_2.3, U203_2.4
Board_2-/REG: C502_2.1, U501_2.1
Board_2-/RF1: C6_2.2, L2_2.2, L3_2.1
Board_2-/RF2: C9_2.2, L3_2.2, L4_2.1
Board_2-/RF_50: C11_2.2, C14_2.1, L4_2.2, R2_2.1
Board_2-/SW: L201_2.1, U201_2.A4
Board_2-/SWDCLK: R601_2.2, U1_2.26
Board_2-/SWDIO: R602_2.2, U1_2.25
Board_2-/TS: R207_2.2, R208_2.1, TH201_2.1, U201_2.C3
Board_2-/VBAT: C202_2.1, C501_2.1, JP201_2.2, TP706_2.1, U201_2.B1, U201_2.B2, U501_2.6, U501_2.10
Board_2-/VDD_2V0: C3_2.2, C4_2.1, C7_2.1, C8_2.1, C10_2.1, C211_2.1, C401_2.1, C402_2.1, R203_2.1, R204_2.1, U1_2.10, U1_2.22, U1_2.36, U1_2.47, U1_2.48, U203_2.1, U401_2.2, U401_2.3, U401_2.9, U401_2.10
Board_2-/VIN: C201_2.1, D601_2.1, J601_2.1, R207_2.1, U201_2.A2
Board_2-/VLED: C208_2.1, D702_2.1, U201_2.C5
Board_2-/VSYS: C205_2.1, L201_2.2, U201_2.B5
Board_2-/XC1: U1_2.34, X2_2.1
Board_2-/XC2: U1_2.35, X2_2.3
Board_2-/XL1: U1_2.1, X1_2.2
Board_2-/XL2: U1_2.2, X1_2.1
Board_2-/nRESET: R1_2.2, TP701_2.1
Board_2-/nRESET_IC: C13_2.2, R1_2.1, U1_2.30
Board_3-/ACC_INT1: U1_3.27, U401_3.12
Board_3-/ACC_INT2: TP401_3.1, U1_3.24, U401_3.11
Board_3-/ANT: L2_3.1, U1_3.31
Board_3-/ANT_FEED: AE1_3.1, C15_3.1, R2_3.2
Board_3-/BATT_P: JP201_3.1, TP201_3.1
Board_3-/CHG_CD: U1_3.39, U201_3.E2
Board_3-/CHG_MR: TP203_3.1, U201_3.E1
Board_3-/DCC: L1_3.1, U1_3.46
Board_3-/DECA: C2_3.2, C5_3.2, C12_3.2, FB1_3.2, U1_3.33, U1_3.43
Board_3-/DECD: C1_3.2, FB1_3.1, L1_3.2, U1_3.45
Board_3-/DOCK_PG: U1_3.7, U201_3.D4
Board_3-/GND: C1_3.1, C2_3.1, C3_3.1, C4_3.2, C5_3.1, C6_3.1, C7_3.2, C8_3.2, C9_3.1, C10_3.2, C11_3.1, C12_3.1, C13_3.1, C14_3.2, C15_3.2, C201_3.2, C202_3.2, C205_3.2, C206_3.2, C208_3.2, C209_3.2, C210_3.2, C211_3.2, C401_3.2, C402_3.2, C501_3.2, C502_3.2, D601_3.2, D602_3.2, D603_3.2, J601_3.2, R202_3.2, R208_3.2, R211_3.2, TH201_3.2, TP202_3.1, TP707_3.1, U1_3.32, U1_3.44, U1_3.49, U201_3.A1, U201_3.A5, U201_3.C2, U201_3.D1, U201_3.D5, U202_3.6, U202_3.7, U202_3.11, U203_3.2, U203_3.5, U401_3.5, U401_3.6, U401_3.7, U401_3.8, U501_3.4, U501_3.8, X2_3.2, X2_3.4
Board_3-/HAPT_EN: U1_3.8, U501_3.5
Board_3-/I2C_SCL: R204_3.2, U1_3.5, U201_3.E5, U202_3.8, U401_3.1, U501_3.2
Board_3-/I2C_SDA: R203_3.2, U1_3.9, U201_3.E4, U202_3.9, U401_3.4, U501_3.3
Board_3-/ISET: R202_3.1, U201_3.C1
Board_3-/LED_B: D702_3.2, U202_3.4
Board_3-/LED_EN: R211_3.1, U1_3.38, U202_3.1
Board_3-/LED_G: D702_3.3, U202_3.3
Board_3-/LED_R: D702_3.4, U202_3.5
Board_3-/LRA_N: TP502_3.1, U501_3.9
Board_3-/LRA_P: TP501_3.1, U501_3.7
Board_3-/LS_CTRL: U1_3.13, U201_3.E3
Board_3-/PAD_SWDCLK: D602_3.1, J601_3.3, R601_3.1
Board_3-/PAD_SWDIO: D603_3.1, J601_3.4, R602_3.1
Board_3-/PMIC_INT: U1_3.6, U201_3.D2
Board_3-/PMID: C206_3.1, C209_3.1, C210_3.1, TP705_3.1, U201_3.A3, U201_3.B3, U201_3.B4, U201_3.C4, U202_3.2, U203_3.3, U203_3.4
Board_3-/REG: C502_3.1, U501_3.1
Board_3-/RF1: C6_3.2, L2_3.2, L3_3.1
Board_3-/RF2: C9_3.2, L3_3.2, L4_3.1
Board_3-/RF_50: C11_3.2, C14_3.1, L4_3.2, R2_3.1
Board_3-/SW: L201_3.1, U201_3.A4
Board_3-/SWDCLK: R601_3.2, U1_3.26
Board_3-/SWDIO: R602_3.2, U1_3.25
Board_3-/TS: R207_3.2, R208_3.1, TH201_3.1, U201_3.C3
Board_3-/VBAT: C202_3.1, C501_3.1, JP201_3.2, TP706_3.1, U201_3.B1, U201_3.B2, U501_3.6, U501_3.10
Board_3-/VDD_2V0: C3_3.2, C4_3.1, C7_3.1, C8_3.1, C10_3.1, C211_3.1, C401_3.1, C402_3.1, R203_3.1, R204_3.1, U1_3.10, U1_3.22, U1_3.36, U1_3.47, U1_3.48, U203_3.1, U401_3.2, U401_3.3, U401_3.9, U401_3.10
Board_3-/VIN: C201_3.1, D601_3.1, J601_3.1, R207_3.1, U201_3.A2
Board_3-/VLED: C208_3.1, D702_3.1, U201_3.C5
Board_3-/VSYS: C205_3.1, L201_3.2, U201_3.B5
Board_3-/XC1: U1_3.34, X2_3.1
Board_3-/XC2: U1_3.35, X2_3.3
Board_3-/XL1: U1_3.1, X1_3.2
Board_3-/XL2: U1_3.2, X1_3.1
Board_3-/nRESET: R1_3.2, TP701_3.1
Board_3-/nRESET_IC: C13_3.2, R1_3.1, U1_3.30

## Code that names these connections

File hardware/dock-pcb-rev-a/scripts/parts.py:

"""WakeBand dock rev A PCB: parts and netlist (single source for schematic and board)."""
# (ref, lib:symbol, value, footprint, LCSC, MPN, {pin: net}, [nc pins], description)
R0402 = "Resistor_SMD:R_0402_1005Metric"
C0402 = "Capacitor_SMD:C_0402_1005Metric"
C0603 = "Capacitor_SMD:C_0603_1608Metric"
SOT6 = "Package_TO_SOT_SMD:SOT-23-6"
def R(ref, val, lcsc, a, b, desc=""): return (ref, "Device:R", val, R0402, lcsc, "", {"1": a, "2": b}, [], desc)
def C(ref, val, lcsc, a, b="GND", fp=C0402, desc=""): return (ref, "Device:C", val, fp, lcsc, "", {"1": a, "2": b}, [], desc)

RP_GPIO_NC = [2, 3, 5, 6, 7, 8, 9, 11, 12, 13, 14, 18, 28, 29, 30, 31, 32, 34, 35, 36, 37, 38, 39, 40, 41]
PARTS = [
    ("U1", "MCU_RaspberryPi:RP2040", "RP2040", "Package_DFN_QFN:QFN-56-1EP_7x7mm_P0.4mm_EP3.2x3.2mm", "C2040", "Raspberry Pi RP2040",
     {**{p: "+3V3" for p in ("1", "10", "22", "33", "42", "49", "43", "44", "48")},
      "4": "LED_USB", "15": "SWCLK_3V3", "16": "SWDIO_3V3", "17": "SWDIO_DRV", "27": "LED_ACT",
      "19": "GND", "20": "XIN", "21": "XOUT", "23": "+1V1", "50": "+1V1", "45": "+1V1",
      "24": "RP_SWCLK", "25": "RP_SWDIO", "26": "RUN", "46": "USB_DM_MCU", "47": "USB_DP_MCU",
      "51": "QSPI_SD3", "52": "QSPI_SCLK", "53": "QSPI_SD0", "54": "QSPI_SD2", "55": "QSPI_SD1", "56": "QSPI_SS",
      "57": "GND"},
     [str(p) for p in RP_GPIO_NC], "CMSIS-DAP SWD probe (Raspberry Pi debugprobe firmware, Debug Probe pin map)"),
    ("U2", "Memory_Flash:W25Q16JVSS", "W25Q16JVSNIQ", "Package_SO:SOIC-8_3.9x4.9mm_P1.27mm", "C2456211", "Winbond W25Q16JVSNIQ",
     {"1": "QSPI_SS", "2": "QSPI_SD1", "3": "QSPI_SD2", "4": "GND", "5": "QSPI_SD0", "6": "QSPI_SCLK", "7": "QSPI_SD3", "8": "+3V3"}, [],
     "2 MB QSPI flash for the RP2040 (debugprobe uses the W25Q080 boot stage)"),
    ("Y1", "Device:Crystal_GND24", "12MHz 12pF", "Crystal:Crystal_SMD_3225-4Pin_3.2x2.5mm", "C2981639", "3225-12-12-10-10/A",
     {"1": "XIN", "3": "XOUT_X", "2": "GND", "4": "GND"}, [], "RP2040 USB clock, 12 MHz"),
    C("C1", "15pF", "C1548", "XIN"), C("C2", "15pF", "C1548", "XOUT_X"),
    R("R1", "1k", "C11702", "XOUT", "XOUT_X", "crystal drive limit (as on the Pico)"),
    ("J1", "Connector:USB_C_Receptacle_USB2.0_16P", "USB-C", "dock:USB_C_Receptacle_HRO_TYPE-C-31-M-12", "C165948", "HRO TYPE-C-31-M-12",
     {"A4": "VBUS", "A9": "VBUS", "B4": "VBUS", "B9": "VBUS", "A1": "GND", "A12": "GND", "B1": "GND", "B12": "GND", "SH": "GND",
      "A5": "CC1", "B5": "CC2", "A6": "USB_DP", "B6": "USB_DP", "A7": "USB_DM", "B7": "USB_DM"}, ["A8", "B8"], "USB 2.0 device, 5 V sink"),
    R("R2", "5.1k", "C25905", "CC1", "GND", "CC1 sink pull-down"), R("R3", "5.1k", "C25905", "CC2", "GND", "CC2 sink pull-down"),
    ("U3", "Power_Protection:USBLC6-2SC6", "USBLC6-2SC6", SOT6, "C7519", "ST USBLC6-2SC6",
     {"1": "USB_DP", "6": "USB_DP", "3": "USB_DM", "4": "USB_DM", "5": "VBUS", "2": "GND"}, [], "USB ESD"),
    R("R4", "27", "C25100", "USB_DP", "USB_DP_MCU"), R("R5", "27", "C25100", "USB_DM", "USB_DM_MCU"),
    ("F1", "Device:Polyfuse", "500mA", "Fuse:Fuse_0805_2012Metric", "C181350", "FSMD050-0805-R", {"1": "VBUS", "2": "VBUS_F"}, [], "USB input fuse"),
    C("C3", "10uF", "C19702", "VBUS_F", fp=C0603),
    ("U4", "Regulator_Linear:XC6206PxxxMR", "XC6206P332MR", "Package_TO_SOT_SMD:SOT-23-3", "C2897477", "Torex XC6206P332MR",
     {"3": "VBUS_F", "2": "+3V3", "1": "GND"}, [], "3.3 V for the RP2040, flash and the 3.3 V side of the translators"),
    C("C4", "1uF", "C52923", "+3V3"),
    ("U5", "Regulator_Linear:XC6206PxxxMR", "XC6206P182MR", "Package_TO_SOT_SMD:SOT-23-3", "C21659", "Torex XC6206P182MR",
     {"3": "+3V3", "2": "+1V8", "1": "GND"}, [], "1.8 V reference for the band side of the SWD translators (the 4 pins carry no VTref)"),
    C("C5", "1uF", "C52923", "+1V8"),
    ("U6", "dock:SY6280AAC", "SY6280AAC", "Package_TO_SOT_SMD:SOT-23-5", "C55136", "Silergy SY6280AAC",
     {"5": "VBUS_F", "4": "VBUS_F", "3": "ISET", "2": "GND", "1": "VIN_BAND"}, [], "current-limited 5 V switch to the band's VIN pin"),
    R("R6", "15k", "C25756", "ISET", "GND", "limit = 6800 / 15k = 0.45 A (SY6280 minimum 0.4 A)"),
    C("C6", "1uF", "C52923", "VBUS_F"), C("C7", "1uF", "C52923", "VIN_BAND"),
    C("C8", "100nF", "C1525", "+3V3"), C("C9", "100nF", "C1525", "+3V3"), C("C10", "100nF", "C1525", "+3V3"),
    C("C11", "100nF", "C1525", "+3V3"), C("C12", "100nF", "C1525", "+3V3"), C("C13", "100nF", "C1525", "+3V3"),
    C("C14", "1uF", "C52923", "+3V3", desc="VREG_VIN"), C("C15", "1uF", "C52923", "+1V1", desc="VREG_VOUT / DVDD"),
    C("C16", "100nF", "C1525", "+1V1"), C("C17", "100nF", "C1525", "+3V3", desc="flash"),
    R("R7", "10k", "C25744", "+3V3", "RUN"), R("R8", "10k", "C25744", "+3V3", "QSPI_SS"),
    R("R9", "1k", "C11702", "QSPI_SS", "BOOT"),
    ("SW1", "Switch:SW_Push", "BOOTSEL", "Button_Switch_SMD:SW_SPST_TS-1088-xR020", "C720477", "XKB TS-1088-AR02016",
     {"1": "BOOT", "2": "GND"}, [], "hold while plugging in USB to get the UF2 drive"),
    ("U7", "Logic_LevelTranslator:SN74LVC1T45DBV", "74LVC1T45", SOT6, "C168856", "Diodes 74LVC1T45W6-7",
     {"1": "+3V3", "2": "GND", "3": "SWCLK_3V3", "4": "SWCLK_1V8", "5": "+3V3", "6": "+1V8"}, [], "SWCLK 3.3 V to 1.8 V, A to B"),
    ("U8", "Logic_LevelTranslator:TXS0101DBV", "TXS0101", SOT6, "C132604", "TI TXS0101DBVR",
     {"1": "+1V8", "2": "GND", "3": "SWDIO_1V8", "4": "SWDIO_3V3", "5": "+1V8", "6": "+3V3"}, [], "SWDIO, auto-direction (debugprobe has no direction pin)"),
    C("C18", "100nF", "C1525", "+3V3"), C("C19", "100nF", "C1525", "+1V8"), C("C20", "100nF", "C1525", "+3V3"), C("C21", "100nF", "C1525", "+1V8"),
    R("R10", "22", "C25092", "SWDIO_DRV", "SWDIO_3V3", "GPIO14 drives, GPIO13 (SWDI) reads the same node"),
    R("R11", "22", "C25092", "SWCLK_1V8", "P_SWCLK"), R("R12", "22", "C25092", "SWDIO_1V8", "P_SWDIO"),
    ("D1", "Device:LED", "red USB", "LED_SMD:LED_0603_1608Metric", "C2286", "KENTO KT-0603R", {"1": "LED_USB_K", "2": "LED_USB"}, [], "USB connected (GPIO2)"),
    R("R13", "1k", "C11702", "LED_USB_K", "GND"),
    ("D2", "Device:LED", "red ACT", "LED_SMD:LED_0603_1608Metric", "C2286", "KENTO KT-0603R", {"1": "LED_ACT_K", "2": "LED_ACT"}, [], "DAP running (GPIO16)"),
    R("R14", "1k", "C11702", "LED_ACT_K", "GND"),
    ("P1", "Connector_Generic:Conn_01x01", "SWCLK", "dock:SpringPin_Mill-Max_0906_PTH_D1.4mm_Drill0.6mm", "", "Mill-Max 0906-4-15-20-75-14-11-0", {"1": "P_SWCLK"}, [], "spring pin to the band's SWDCLK contact"),
    ("P2", "Connector_Generic:Conn_01x01", "SWDIO", "dock:SpringPin_Mill-Max_0906_PTH_D1.4mm_Drill0.6mm", "", "Mill-Max 0906-4-15-20-75-14-11-0", {"1": "P_SWDIO"}, [], "spring pin to SWDIO"),
    ("P3", "Connector_Generic:Conn_01x01", "GND", "dock:SpringPin_Mill-Max_0906_PTH_D1.4mm_Drill0.6mm", "", "Mill-Max 0906-4-15-20-75-14-11-0", {"1": "GND"}, [], "spring pin to GND"),
    ("P4", "Connector_Generic:Conn_01x01", "VIN", "dock:SpringPin_Mill-Max_0906_PTH_D1.4mm_Drill0.6mm", "", "Mill-Max 0906-4-15-20-75-14-11-0", {"1": "VIN_BAND"}, [], "spring pin to VIN (5 V, 0.45 A limit)"),
    ("TP1", "Connector_Generic:Conn_01x01", "RP_SWCLK", "TestPoint:TestPoint_Pad_D1.0mm", "", "", {"1": "RP_SWCLK"}, [], "RP2040 SWD (recovery)"),
    ("TP2", "Connector_Generic:Conn_01x01", "RP_SWDIO", "TestPoint:TestPoint_Pad_D1.0mm", "", "", {"1": "RP_SWDIO"}, [], "RP2040 SWD (recovery)"),
    ("TP3", "Connector_Generic:Conn_01x01", "RUN", "TestPoint:TestPoint_Pad_D1.0mm", "", "", {"1": "RUN"}, [], "RP2040 reset"),
    ("TP4", "Connector_Generic:Conn_01x01", "GND", "TestPoint:TestPoint_Pad_D1.0mm", "", "", {"1": "GND"}, [], "ground"),
]
FLAGS = ["VBUS", "VBUS_F", "GND"]

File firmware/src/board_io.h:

/* Board GPIOs from the devicetree node "nudgeband-io" (boards/nudgeband). */
#ifndef NUDGEBAND_BOARD_IO_H
#define NUDGEBAND_BOARD_IO_H

#include <zephyr/device.h>
#include <zephyr/drivers/gpio.h>
#include <zephyr/drivers/i2c.h>

extern const struct gpio_dt_spec io_pmic_int;
extern const struct gpio_dt_spec io_dock_pg;
extern const struct gpio_dt_spec io_acc_int1;
extern const struct gpio_dt_spec io_acc_int2;
extern const struct gpio_dt_spec io_hapt_en;
extern const struct gpio_dt_spec io_led_en;
extern const struct gpio_dt_spec io_chg_cd;
extern const struct gpio_dt_spec io_ls_ctrl;

/* The one I2C bus: LIS2DW12 0x19, DRV2605L 0x5A, IS31FL3193 0x68, BQ25125 0x6A. */
extern const struct device *const i2c_bus;

int board_io_init(void);

#endif
